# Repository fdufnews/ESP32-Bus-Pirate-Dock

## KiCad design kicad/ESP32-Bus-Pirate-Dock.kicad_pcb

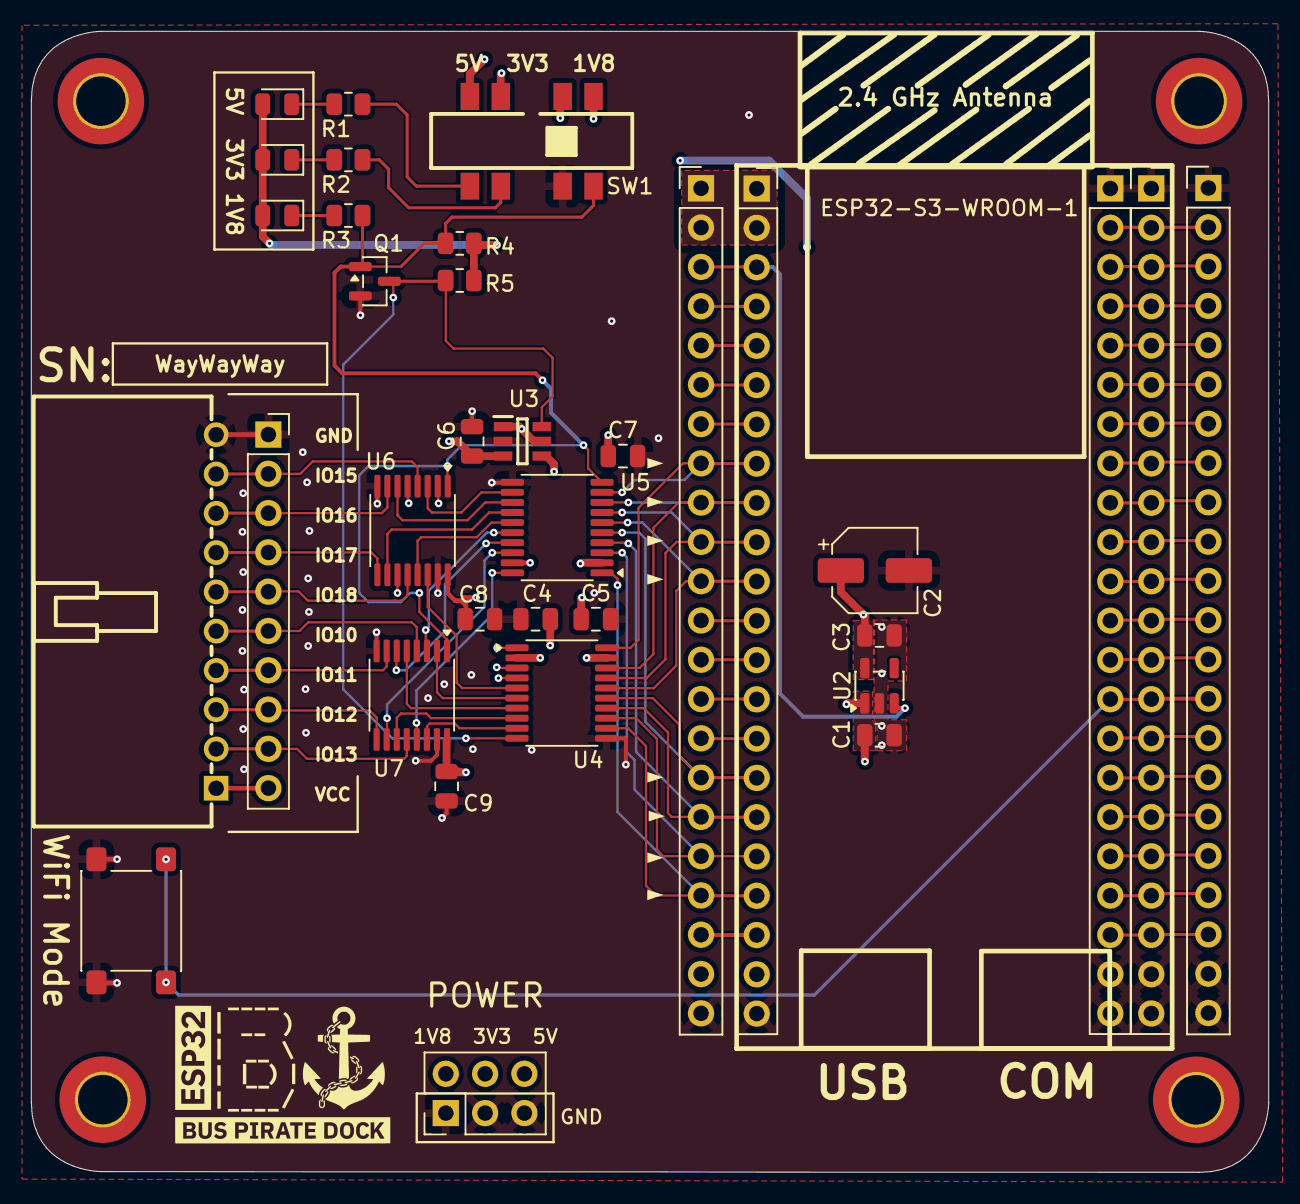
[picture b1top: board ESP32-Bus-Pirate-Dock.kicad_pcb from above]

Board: 4 copper layers, 80.0 x 73.8 mm, 38 parts (0 on the bottom side), 74 nets.

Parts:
C1, C3: 1u; C_0805_2012Metric
C2: 22u; CP_Elec_5x4.5
C4, C5, C6, C7: 0.1u; C_0805_2012Metric
C8, C9: 4.7u; C_0805_2012Metric
CN1: HX25418-10WA; CONN-TH_HX25418-10WA
D1: RED; LED_0805_2012Metric
D2: ORANGE; LED_0805_2012Metric
D3: BLUE; LED_0805_2012Metric
H1, H2, H3, H4: MountingHole; MountingHole_3.2mm_M3_DIN965_Pad_TopBottom
J1, J5, J6: Conn_01x22; PinSocket_1x22_P2.54mm_Vertical
J2, J4: Conn_01x22; PinHeader_1x22_P2.54mm_Vertical
J3: Conn_01x10V; PinSocket_1x10_P2.54mm_Vertical
J7: Conn_02x03; PinHeader_2x03_P2.54mm_Vertical
Q1: 2N7002; SOT-23
R1, R2, R3: 1k; R_0805_2012Metric
R4, R5: 10k; R_0805_2012Metric
SW1: TA-3532S-A2; SW-SMD_8P-L13.0-W3.5-P2.00
SW_1: SW_BOOT; SW_SPST_PTS645Sx43SMTR92
U2: TLV75518PDBV; SOT-23-5
U3: TS5A3157DBVR; SOT95P280X145-6N
U4, U5: TXS0108EPW; Texas_PW0020A_TSSOP-20_4.4x6.5mm_P0.65mm
U6, U7: TMUX1574PW; TSSOP-16_4.4x5mm_P0.65mm

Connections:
+1V8: C2.1, C3.1, C4.1, J7.2, SW1.1, U2.5 (OUT), U4.2 (VCCA)
+3.3V: C5.1, C7.1, C8.1, C9.1, D1.2 (A), D2.2 (A), D3.2 (A), J1.1, J1.2, J2.1, J2.2, J7.4, R4.2, R5.2, SW1.3, U3.1 (NO), U3.5 (V+), U4.19 (VCCB), U5.2 (VCCA), U6.16 (VDD), U7.16 (VDD)
+5V: C1.1, J1.21, J2.21, J7.6, SW1.4, U2.1 (IN)
/Voltage Level Translator/3V3_SEL: R2.2, SW1.6
/Voltage Level Translator/5V_SEL: R1.2, SW1.5
/Voltage Level Translator/D1_K: D3.1 (K), R3.2
/Voltage Level Translator/D2_K: D2.1 (K), R2.1
/Voltage Level Translator/D3_K: D1.1 (K), R1.1
/Voltage Level Translator/IO10_H: U5.16 (B4), U7.3 (S1B)
/Voltage Level Translator/IO10_L: U4.6 (A5), U7.2 (S1A)
/Voltage Level Translator/IO11_H: U5.17 (B3), U7.6 (S2B)
/Voltage Level Translator/IO11_L: U4.7 (A6), U7.5 (S2A)
/Voltage Level Translator/IO12_H: U5.18 (B2), U7.10 (S3B)
/Voltage Level Translator/IO12_L: U4.8 (A7), U7.11 (S3A)
/Voltage Level Translator/IO13_H: U5.20 (B1), U7.13 (S4B)
/Voltage Level Translator/IO13_L: U4.9 (A8), U7.14 (S4A)
/Voltage Level Translator/IO15_H: U5.12 (B8), U6.3 (S1B)
/Voltage Level Translator/IO15_L: U4.1 (A1), U6.2 (S1A)
/Voltage Level Translator/IO16_H: U5.13 (B7), U6.6 (S2B)
/Voltage Level Translator/IO16_L: U4.3 (A2), U6.5 (S2A)
/Voltage Level Translator/IO17_H: U5.14 (B6), U6.10 (S3B)
/Voltage Level Translator/IO17_L: U4.4 (A3), U6.11 (S3A)
/Voltage Level Translator/IO18_H: U5.15 (B5), U6.13 (S4B)
/Voltage Level Translator/IO18_L: U4.5 (A4), U6.14 (S4A)
/Voltage Level Translator/SEL: Q1.1 (G), R3.1, R4.1, SW1.8, U5.10 (OE), U6.1 (SEL), U7.1 (SEL)
/Voltage Level Translator/V_{ccB}_H: U3.4 (COM), U5.19 (VCCB)
/Voltage Level Translator/~SEL: Q1.3 (D), R5.1, U3.6 (IN), U4.10 (OE)
GND: C1.2, C2.2, C3.2, C4.2, C5.2, C6.2, C7.2, C8.2, C9.2, CN1.10, J1.22, J2.22, J3.1, J4.1, J4.21, J4.22, J5.1, J5.21, J5.22, J6.1, J6.21, J6.22, J7.1, J7.3, J7.5, Q1.2 (S), SW1.7, SW_1.2 (D), U2.2 (GND), U3.2 (GND), U4.11 (GND), U5.11 (GND), U6.8 (GND), U6.15 (~EN), U7.8 (GND), U7.15 (~EN)
GPIO0: J4.14, J5.14, J6.14, SW_1.1 (C)
GPIO1: J4.4, J5.4, J6.4
GPIO2: J4.5, J5.5, J6.5
GPIO3: J1.13, J2.13
GPIO4: J1.4, J2.4
GPIO5: J1.5, J2.5
GPIO6: J1.6, J2.6
GPIO7: J1.7, J2.7
GPIO8: J1.12, J2.12
GPIO9: J1.15, J2.15
GPIO10: J1.16, J2.16, U4.15 (B5), U5.5 (A4)
GPIO11: J1.17, J2.17, U4.14 (B6), U5.4 (A3)
GPIO12: J1.18, J2.18, U4.13 (B7), U5.3 (A2)
GPIO13: J1.19, J2.19, U4.12 (B8), U5.1 (A1)
GPIO14: J1.20, J2.20
GPIO15: J1.8, J2.8, U4.20 (B1), U5.9 (A8)
GPIO16: J1.9, J2.9, U4.18 (B2), U5.8 (A7)
GPIO17: J1.10, J2.10, U4.17 (B3), U5.7 (A6)
GPIO18: J1.11, J2.11, U4.16 (B4), U5.6 (A5)
GPIO19: J4.20, J5.20, J6.20
GPIO20: J4.19, J5.19, J6.19
GPIO21: J4.18, J5.18, J6.18
GPIO35: J4.13, J5.13, J6.13
GPIO36: J4.12, J5.12, J6.12
GPIO37: J4.11, J5.11, J6.11
GPIO38: J4.10, J5.10, J6.10
GPIO39: J4.9, J5.9, J6.9
GPIO40: J4.8, J5.8, J6.8
GPIO41: J4.7, J5.7, J6.7
GPIO42: J4.6, J5.6, J6.6
GPIO45: J4.15, J5.15, J6.15
GPIO46: J1.14, J2.14
GPIO47: J4.17, J5.17, J6.17
GPIO48: J4.16, J5.16, J6.16
IO10: CN1.5, J3.6, U7.4 (D1)
IO11: CN1.4, J3.7, U7.7 (D2)
IO12: CN1.3, J3.8, U7.9 (D3)
IO13: CN1.2, J3.9, U7.12 (D4)
IO15: CN1.9, J3.2, U6.4 (D1)
IO16: CN1.8, J3.3, U6.7 (D2)
IO17: CN1.7, J3.4, U6.9 (D3)
IO18: CN1.6, J3.5, U6.12 (D4)
RST: J1.3, J2.3, U2.3 (EN)
U0RX: J4.3, J5.3, J6.3
U0TX: J4.2, J5.2, J6.2
VTARGET: C6.1, CN1.1, J3.10, SW1.2, U3.3 (NC)

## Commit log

2026-03-05 Modified "Solid" to "Thermal Relief" GND Pour
2026-03-06 Deleted vias & added thermal relief spoke
